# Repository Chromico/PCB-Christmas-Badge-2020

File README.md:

# Christmas badge ( 2020 edition )
An open source PCB christmas badge with 5 red LEDs that are powered by a CR2032 coin cell battery. This can also be used as an ornament that you can hang on your christmas tree and so on. 

My website: https://tecknologg.website

# Front 

.png)

# Back

.png)

# Documentation

You can get the official documentation here: https://github.com/Chromico/PCB-Christmas-Badge-2020/blob/main/documentation/Christmas%20badge%20(%202020%20edition%20)%20-%20documentation.pdf

# Certification

# Contact

Need to contact me ? Just send me an email at nathan@tecknologg.website or tecknologg@gmail.com

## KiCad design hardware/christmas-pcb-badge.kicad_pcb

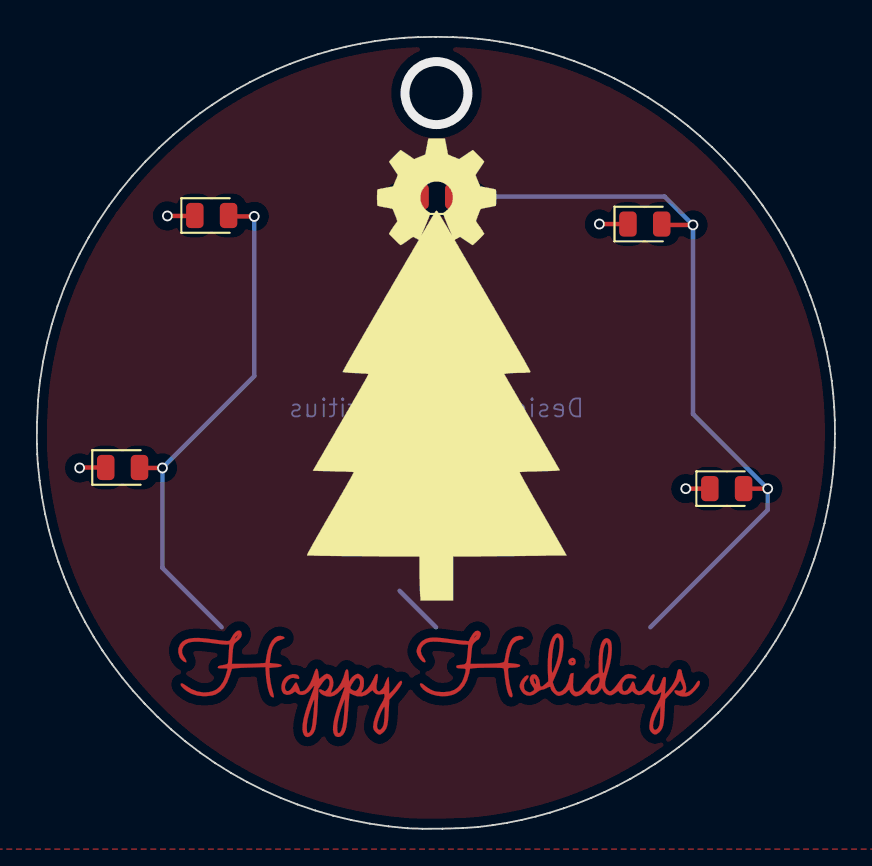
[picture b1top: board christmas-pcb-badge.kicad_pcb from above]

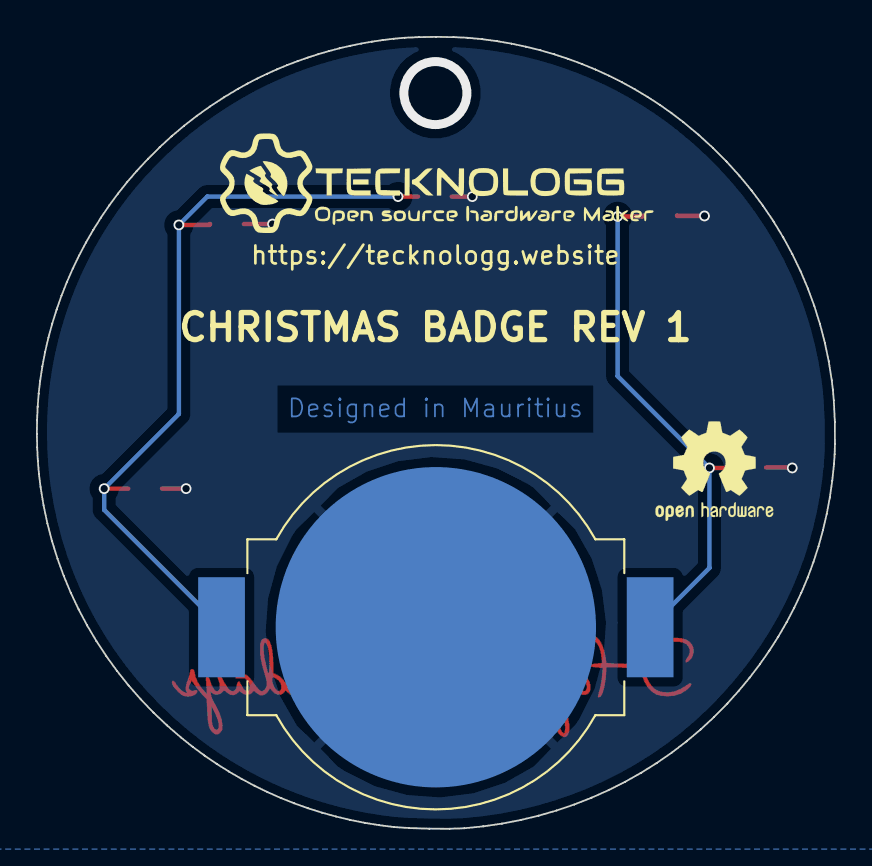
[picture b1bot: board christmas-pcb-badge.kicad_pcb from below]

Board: 2 copper layers, 44.3 x 44.0 mm, 7 parts (2 on the bottom side), 2 nets.

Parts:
BT1: Battery_Cell; BatteryHolder_MPD_BC2003_1x2032
R1, R2, R3, R4, R5: LED_0805_2012Metric
e: LOGO; tecknologg2

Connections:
+3V3: BT1.1, R1.2, R2.2, R3.2, R4.2, R5.2
GND: BT1.2, R1.1, R2.1, R3.1, R4.1, R5.1

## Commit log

2020-12-08 [ImgBot] Optimize images
    *Total -- 2,669.83kb -> 2,327.27kb (12.83%)
    /photos/pcb-christmas-badge-on-removebg-preview (1).png -- 52.88kb -> 45.17kb (14.58%)
    /photos/banner.png -- 2,121.14kb -> 1,832.24kb (13.62%)
    /hardware/christmas-pcb-badge-redbg.png -- 129.10kb -> 115.91kb (10.22%)
    /hardware/christmas-pcb-badge.png -- 313.23kb -> 284.27kb (9.25%)
    /photos/pcb-christmas-badge-on-back-removebg-preview (1).png -- 53.48kb -> 49.68kb (7.11%)
2020-12-08 Create LICENSE
